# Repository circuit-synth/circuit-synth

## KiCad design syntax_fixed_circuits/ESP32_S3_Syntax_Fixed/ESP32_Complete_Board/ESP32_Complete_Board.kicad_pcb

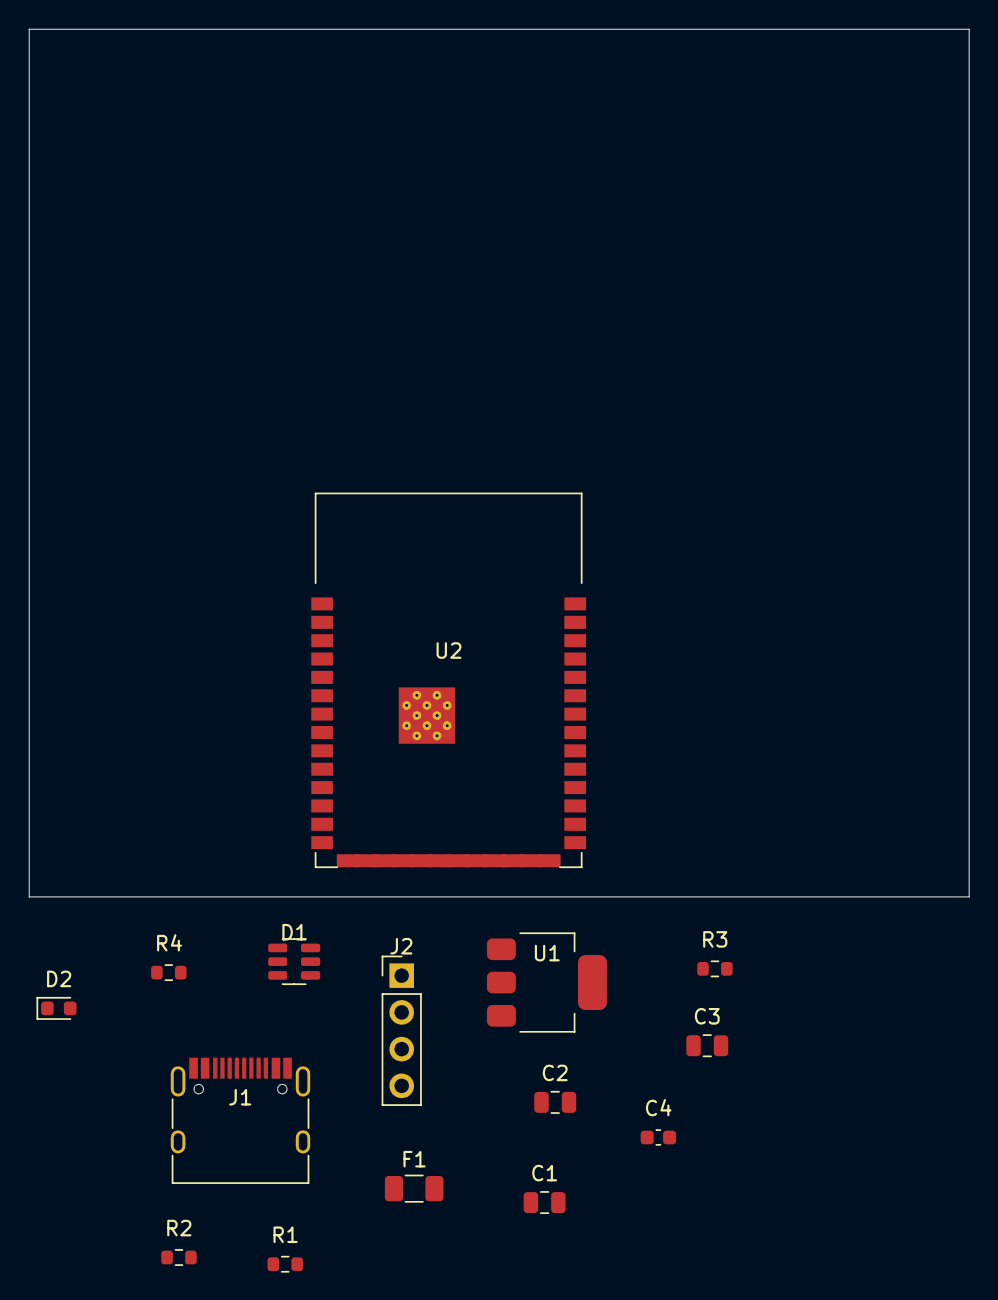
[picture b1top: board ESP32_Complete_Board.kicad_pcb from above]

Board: 2 copper layers, 65.0 x 60.0 mm, 15 parts (0 on the bottom side), 15 nets, no tracks yet.

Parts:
C1, C3: 10uF; C_0805_2012Metric
C2: 22uF; C_0805_2012Metric
C4: 100nF; C_0603_1608Metric
D1: SOT-23-6
D2: LED_0603_1608Metric
F1: 2A; Fuse_1206_3216Metric
J1: USB_C_Receptacle_HRO_TYPE-C-31-M-12
J2: PinHeader_1x04_P2.54mm_Vertical
R1, R2: 5.1k; R_0603_1608Metric
R3: 10k; R_0603_1608Metric
R4: 220; R_0603_1608Metric
U1: SOT-223-3_TabPin2
U2: ESP32-S3-WROOM-1

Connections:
DEBUG_RX: J2.4, U2.36
DEBUG_TX: J2.3, U2.37
GND: C1.2, C2.2, C3.2, C4.2, D1.2, D2.1, J1.A1, J1.A12, J1.B1, J1.B12, J2.2, R1.2, R2.2, U1.1, U2.1, U2.40, U2.41
LED_CONTROL: R4.1, U2.12
unnamed: F1.1, J1.A4, J1.A9, J1.B4, J1.B9
unnamed: D1.1, J1.A6, J1.B6
unnamed: D1.3, J1.A7, J1.B7
unnamed: J1.A5, R1.1
unnamed: J1.B5, R2.1
unnamed: R3.2, U2.3
unnamed: D2.2, R4.2
USB_DM: D1.4, U2.13
USB_DP: D1.6, U2.14
VBUS: C1.1, D1.5, F1.2, U1.3
VCC_3V3: C2.1, C3.1, C4.1, J2.1, R3.1, U1.2, U2.2
